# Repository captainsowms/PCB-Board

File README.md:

# PCB-Board
This Biard was built by Edaefe Efosa.
It is a DE0 GPIO to breadboard adapter, 40 pin adapter.

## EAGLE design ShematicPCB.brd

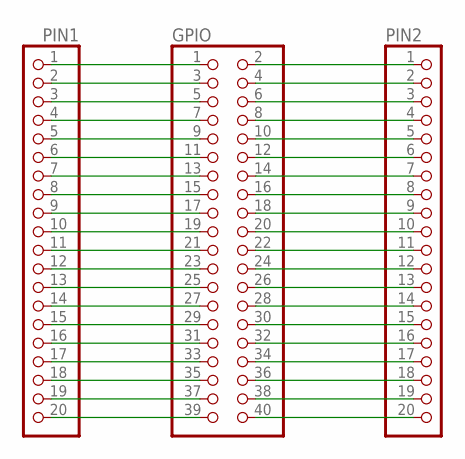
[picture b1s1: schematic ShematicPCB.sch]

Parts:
GPIO: PINHD-2X20; 2X20
PIN1, PIN2: PINHD-1X20; 1X20

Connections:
GND: GPIO.21, PIN1.11
unnamed: GPIO.1, PIN1.1
unnamed: GPIO.9, PIN1.5
unnamed: GPIO.3, PIN1.2
unnamed: GPIO.5, PIN1.3
unnamed: GPIO.7, PIN1.4
unnamed: GPIO.11, PIN1.6
unnamed: GPIO.13, PIN1.7
unnamed: GPIO.15, PIN1.8
unnamed: GPIO.17, PIN1.9
unnamed: GPIO.19, PIN1.10
unnamed: GPIO.2, PIN2.1
unnamed: GPIO.25, PIN1.13
unnamed: GPIO.27, PIN1.14
unnamed: GPIO.29, PIN1.15
unnamed: GPIO.31, PIN1.16
unnamed: GPIO.33, PIN1.17
unnamed: GPIO.35, PIN1.18
unnamed: GPIO.37, PIN1.19
unnamed: GPIO.39, PIN1.20
unnamed: GPIO.40, PIN2.20
unnamed: GPIO.38, PIN2.19
unnamed: GPIO.36, PIN2.18
unnamed: GPIO.34, PIN2.17
unnamed: GPIO.32, PIN2.16
unnamed: GPIO.30, PIN2.15
unnamed: GPIO.28, PIN2.14
unnamed: GPIO.26, PIN2.13
unnamed: GPIO.24, PIN2.12
unnamed: GPIO.22, PIN2.11
unnamed: GPIO.20, PIN2.10
unnamed: GPIO.18, PIN2.9
unnamed: GPIO.16, PIN2.8
unnamed: GPIO.14, PIN2.7
unnamed: GPIO.12, PIN2.6
unnamed: GPIO.10, PIN2.5
unnamed: GPIO.8, PIN2.4
unnamed: GPIO.6, PIN2.3
unnamed: GPIO.4, PIN2.2
VCC: GPIO.23, PIN1.12

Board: 2 copper layers, 3 parts (0 on the bottom side), 40 nets, no tracks yet.

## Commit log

2018-05-02 Create MIT LICENSE
2018-05-02 Update MIT LICENSE
